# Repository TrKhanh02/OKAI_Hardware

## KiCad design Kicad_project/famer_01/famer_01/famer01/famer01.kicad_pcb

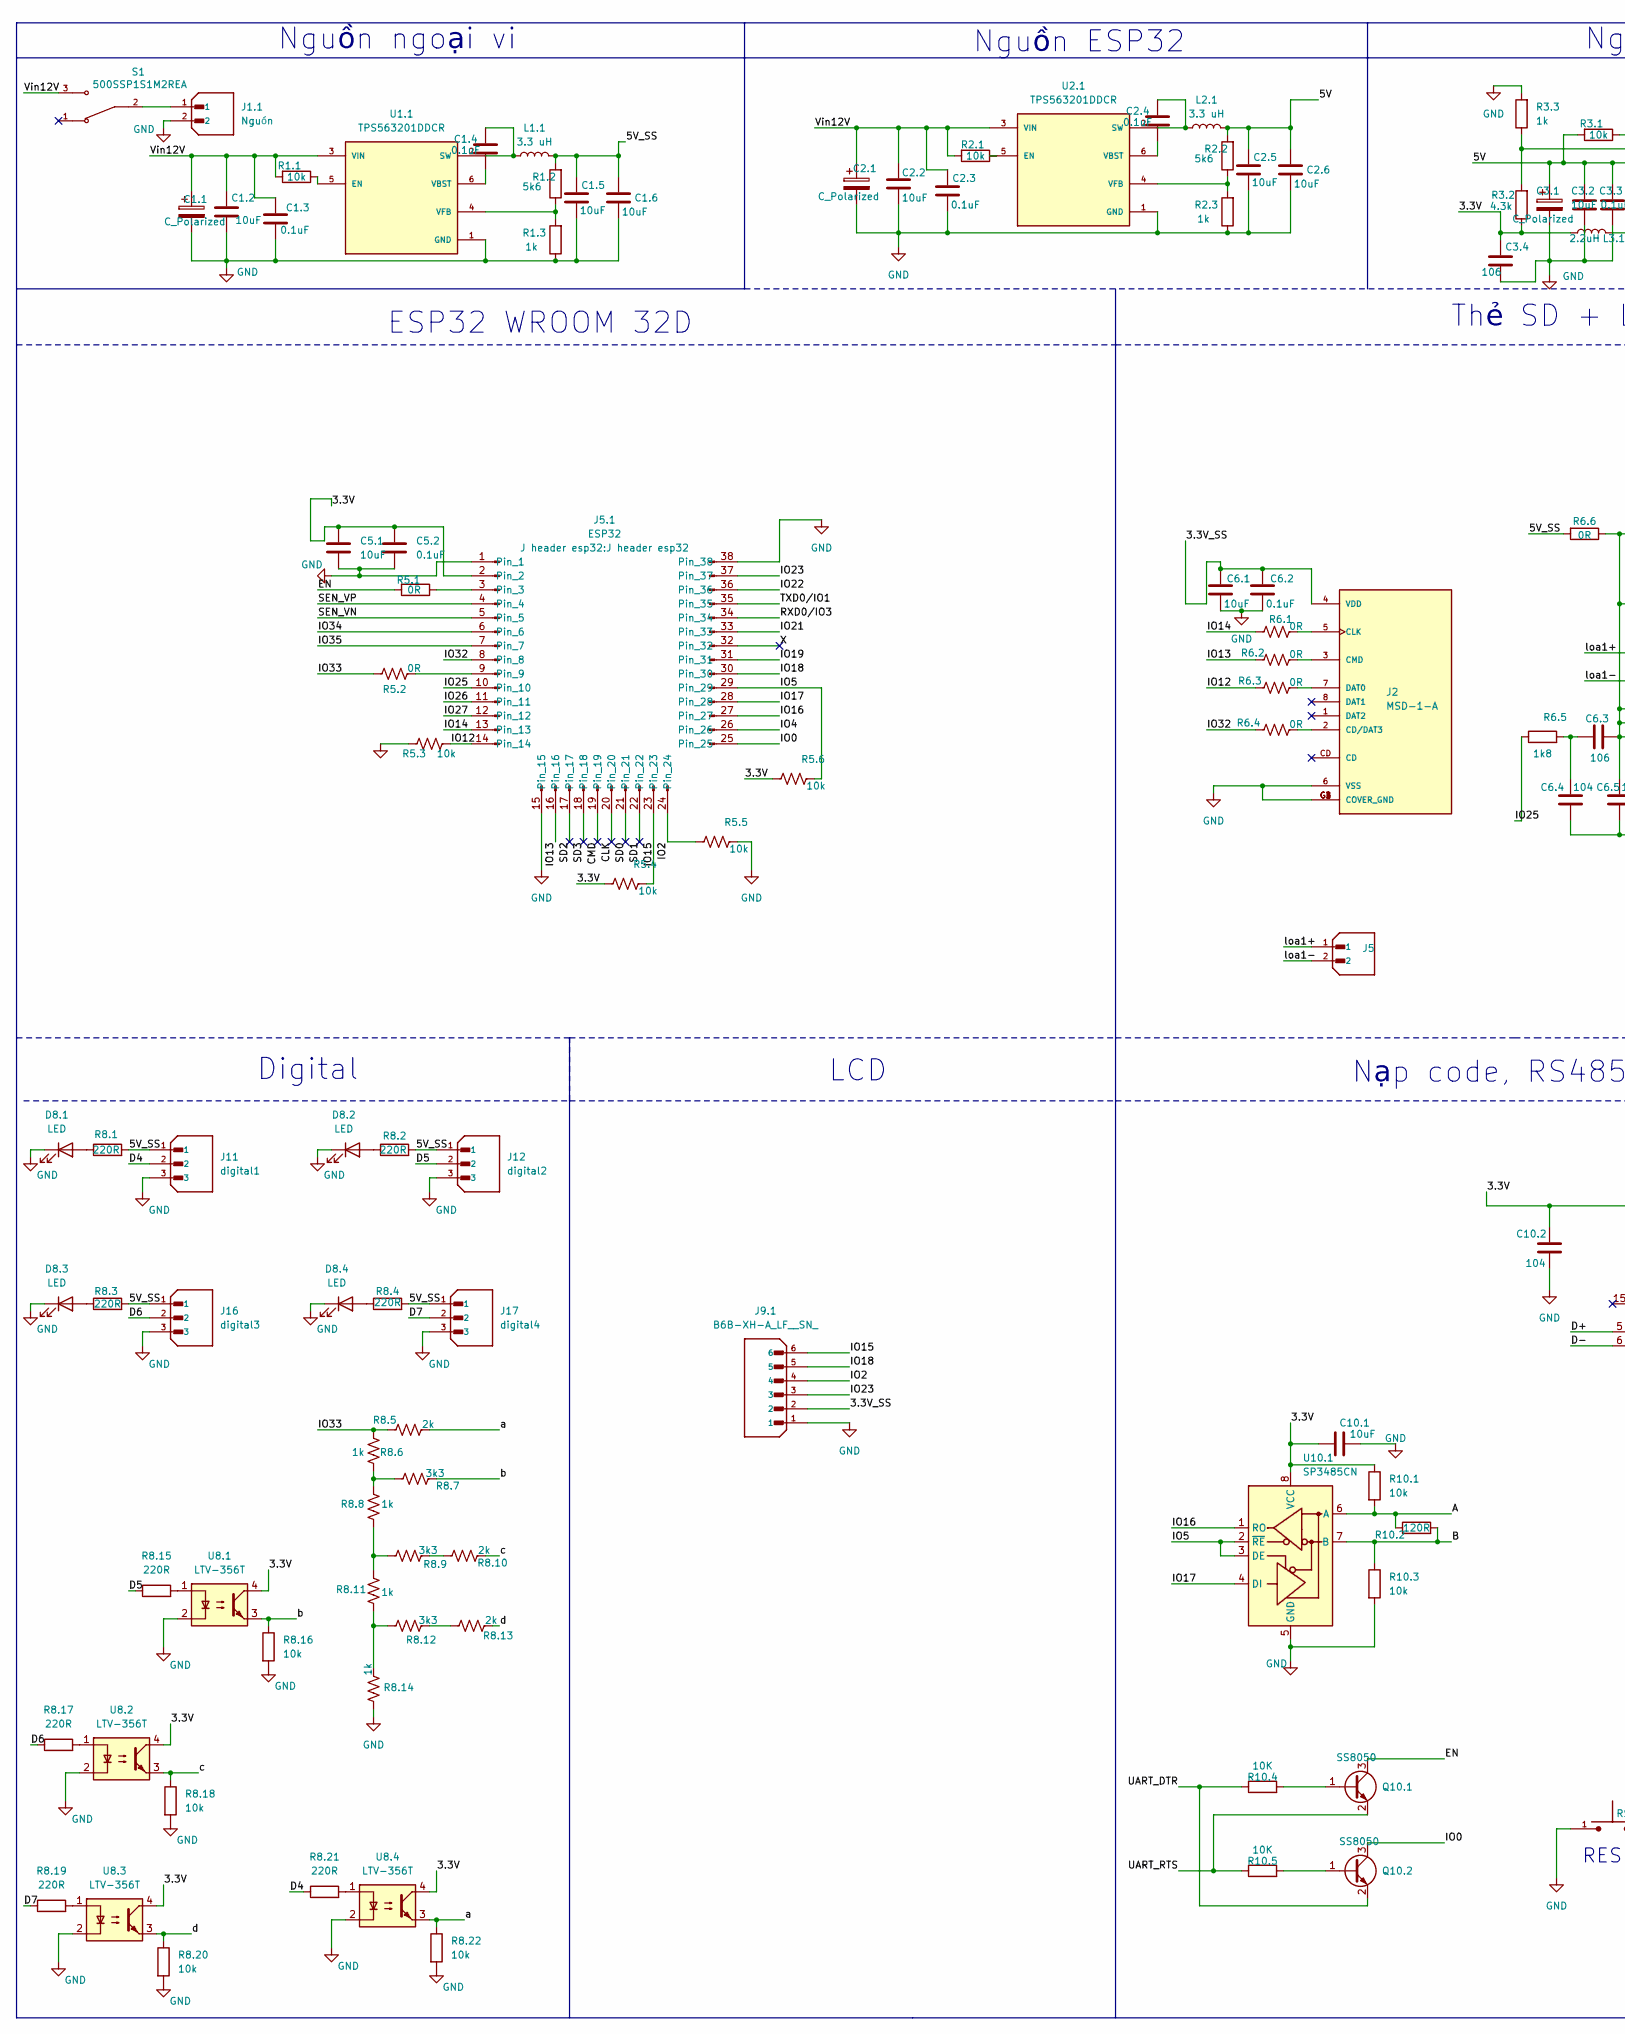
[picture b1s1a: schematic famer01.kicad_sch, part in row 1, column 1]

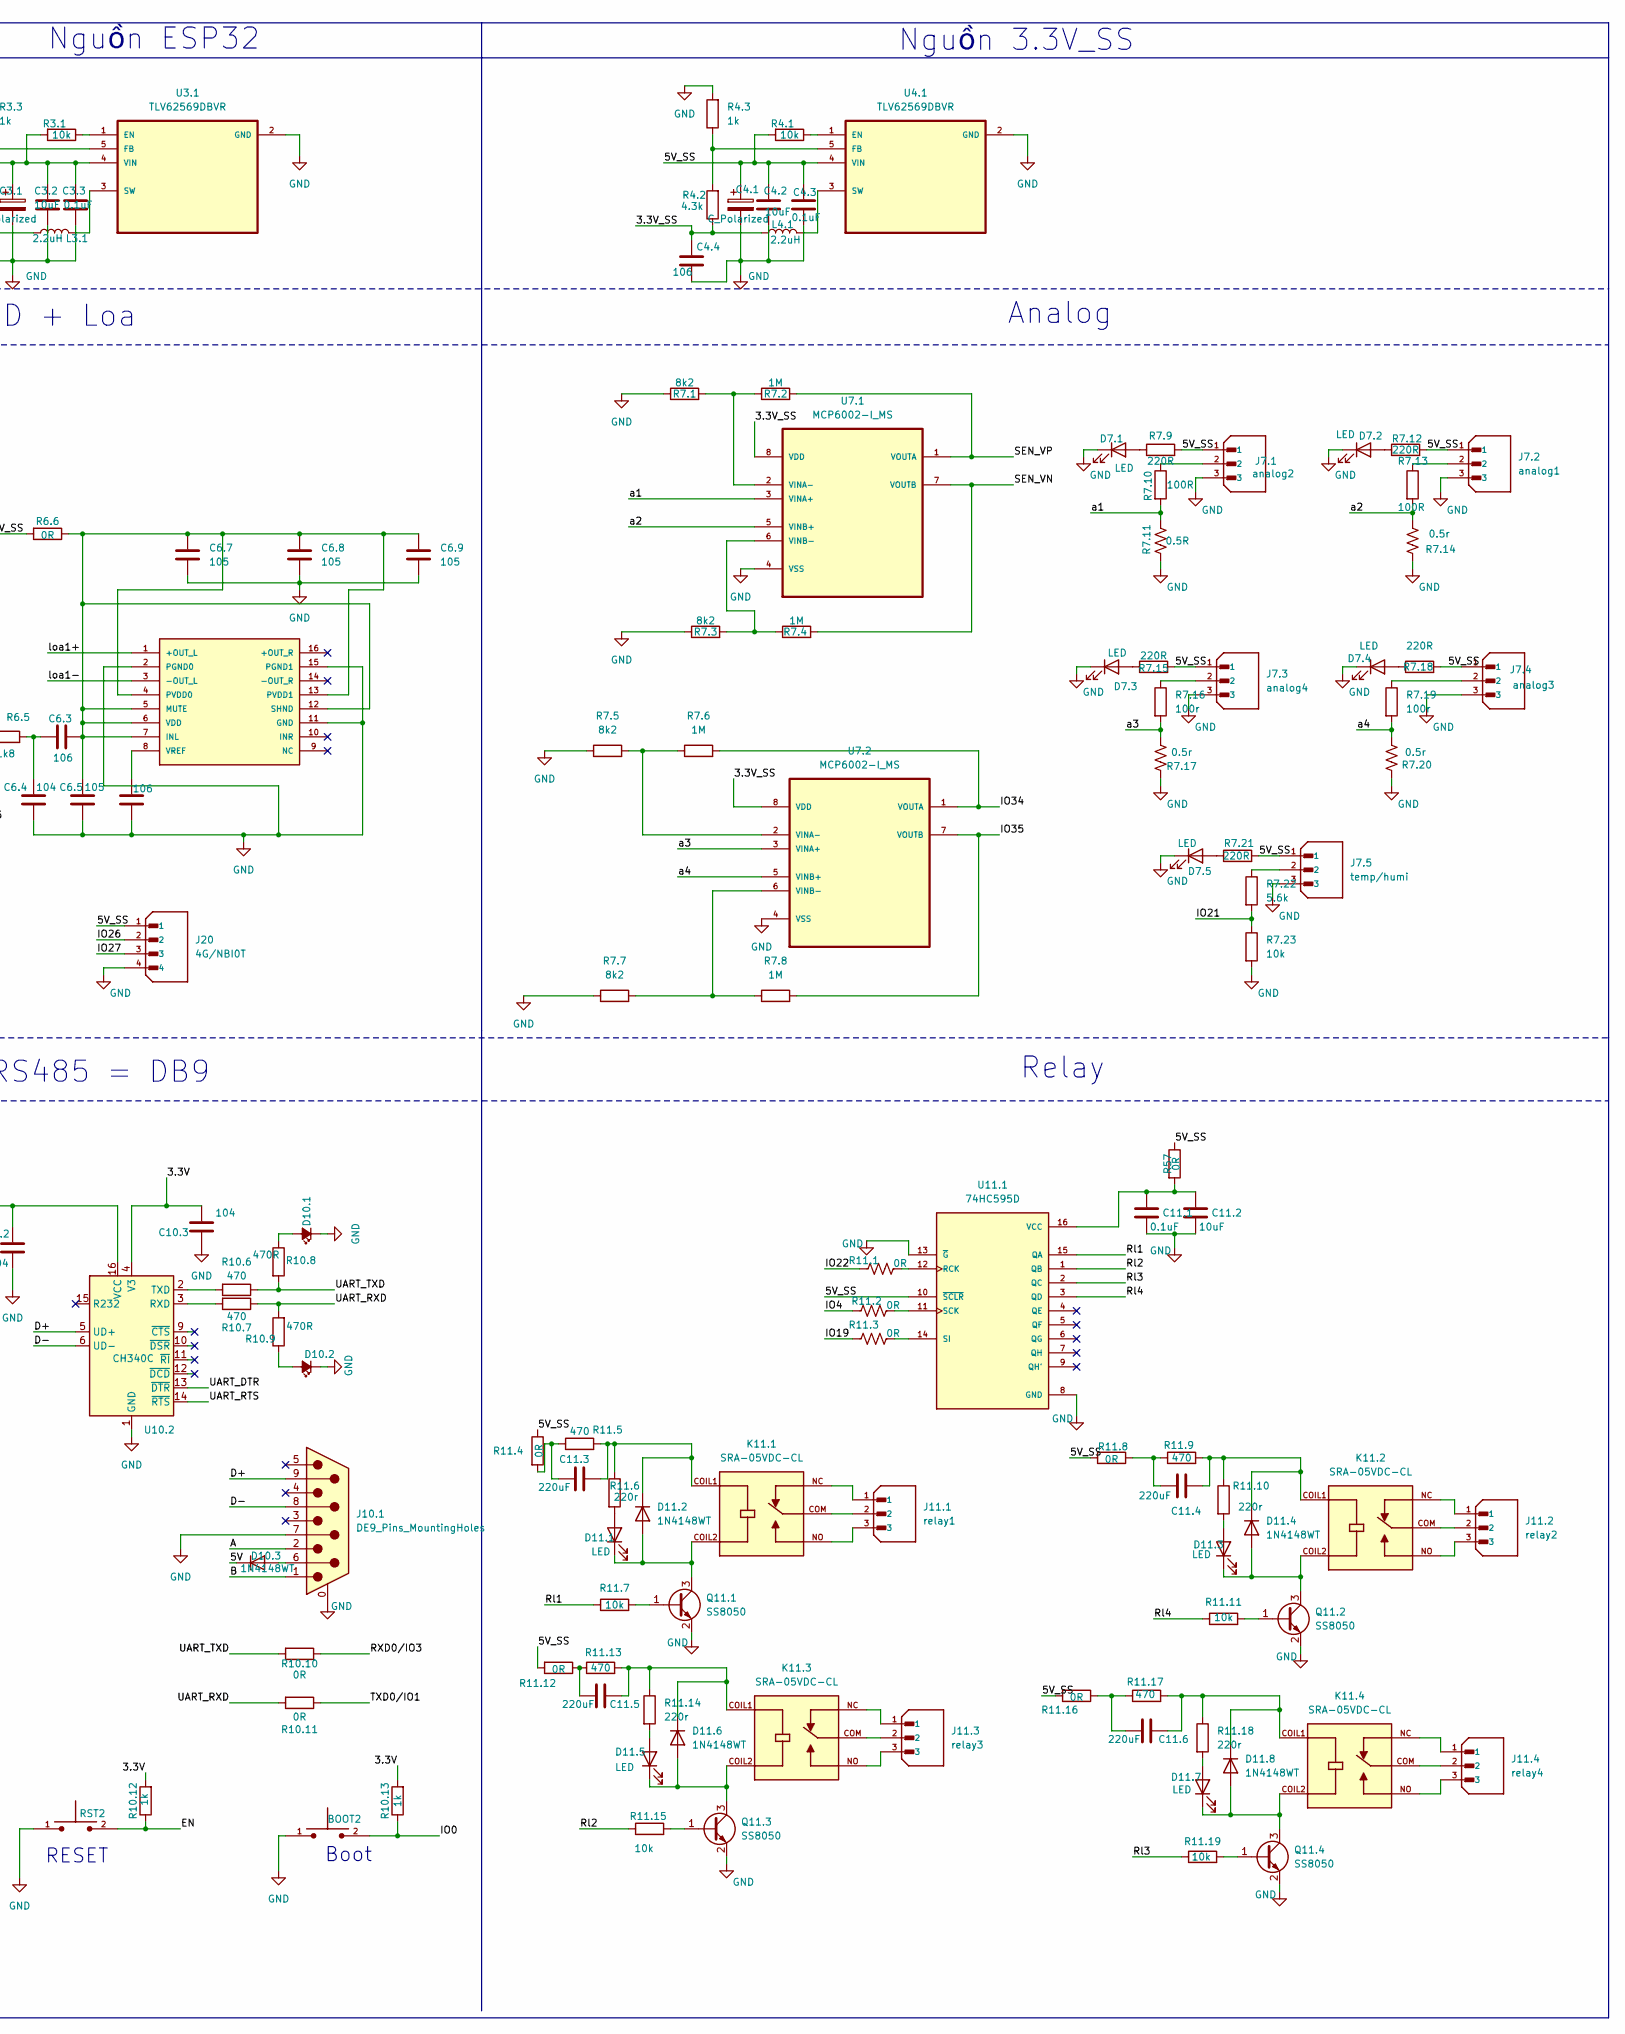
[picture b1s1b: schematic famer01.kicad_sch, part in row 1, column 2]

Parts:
BOOT2: TS10-63-26-BE-250-SMT-TR; SW_TS10-63-26-BE-250-SMT-TR; PARTREV 1.0
C1.1, C2.1, C3.1, C4.1: C_Polarized; CP_Elec_6.3x7.7
C1.2, C1.5, C1.6, C2.2, C2.5, C2.6, C3.2, C4.2, C5.1, C6.1, C10.1, C11.2: 10uF; C_0805_2012Metric_Pad1.18x1.45mm_HandSolder
C1.3, C1.4, C2.3, C2.4, C3.3, C4.3, C5.2, C6.2, C11.1: 0.1uF; C_0805_2012Metric_Pad1.18x1.45mm_HandSolder
C3.4, C4.4, C6.3, C6.6: 106; C_0805_2012Metric_Pad1.18x1.45mm_HandSolder
C6.4, C10.2, C10.3: 104; C_0805_2012Metric_Pad1.18x1.45mm_HandSolder
C6.5, C6.7, C6.8, C6.9: 105; C_0805_2012Metric_Pad1.18x1.45mm_HandSolder
C11.3, C11.4, C11.5, C11.6: 220uF; C_0805_2012Metric_Pad1.18x1.45mm_HandSolder
D7.1, D7.2, D7.3, D7.4, D7.5, D8.1, D8.2, D8.3, D8.4, D11.1, D11.3, D11.5, D11.7: LED; LED_Rectangular_W3.0mm_H2.0mm
D10.1, D10.2: LED_Small_Filled; LED_0805_2012Metric_Pad1.15x1.40mm_HandSolder
D10.3, D11.2, D11.4, D11.6, D11.8: 1N4148WT; D_0805_2012Metric_Pad1.15x1.40mm_HandSolder
J1.1: Nguồn; CUI_TBP04R1-500-02BE; PARTREV N/A
J2: MSD-1-A; CUI_MSD-1-A; PARTREV 1.0
J5: Nguồn; JST_B2B-XH-A; PARTREV N/A
J5.1: ESP32; J header esp32
J7.1: analog2; CUI_TBP04R1-500-03BE; PARTREV 7/4/21
J7.2: analog1; CUI_TBP04R1-500-03BE; PARTREV 7/4/21
J7.3: analog4; CUI_TBP04R1-500-03BE; PARTREV 7/4/21
J7.4: analog3; CUI_TBP04R1-500-03BE; PARTREV 7/4/21
J7.5: temp/humi; CUI_TBP04R1-500-03BE; PARTREV 7/4/21
J9.1: B6B-XH-A_LF__SN_; JST_B6B-XH-A_LF__SN_; PARTREV 7/4/21
J10.1: DE9_Pins_MountingHoles; DSUB-9_Pins_Vertical_P2.77x2.84mm_MountingHoles
J11: digital1; CUI_TBP04R1-500-03BE; PARTREV 7/4/21
J11.1: relay1; CUI_TBP04R1-500-03BE; PARTREV 7/4/21
J11.2: relay2; CUI_TBP04R1-500-03BE; PARTREV 7/4/21
J11.3: relay3; CUI_TBP04R1-500-03BE; PARTREV 7/4/21
J11.4: relay4; CUI_TBP04R1-500-03BE; PARTREV 7/4/21
J12: digital2; CUI_TBP04R1-500-03BE; PARTREV 7/4/21
J16: digital3; CUI_TBP04R1-500-03BE; PARTREV 7/4/21
J17: digital4; CUI_TBP04R1-500-03BE; PARTREV 7/4/21
J20: 4G/NBI0T; JST_B4B-XH-A_LF__SN_; PARTREV 7/4/21
K11.1, K11.2, K11.3, K11.4: SRA-05VDC-CL; RELAY_SRA-05VDC-CL; PARTREV NA
L1.1, L2.1: 3.3 uH; IND_SLF7032T-331MR22-2PF
L3.1, L4.1: 2.2uH; IND_SLF7032T-331MR22-2PF
Q10.1, Q10.2, Q11.1, Q11.2, Q11.3, Q11.4: SS8050; SOT-23
R1.1, R2.1, R3.1, R4.1, R5.3, R5.4, R5.5, R5.6, R7.23, R8.16, R8.18, R8.20, R8.22, R10.1, R10.3, R11.7, R11.11, R11.15, R11.19: 10k; R_0805_2012Metric_Pad1.20x1.40mm_HandSolder
R1.2, R2.2: 5k6; R_0805_2012Metric_Pad1.20x1.40mm_HandSolder
R1.3, R2.3, R3.3, R4.3, R8.6, R8.8, R8.11, R8.14, R10.12, R10.13: 1k; R_0805_2012Metric_Pad1.20x1.40mm_HandSolder
R3.2, R4.2: 4.3k; R_0805_2012Metric_Pad1.20x1.40mm_HandSolder
R5.1, R5.2, R6.1, R6.2, R6.3, R6.4, R6.6, R10.10, R10.11, R11.1, R11.2, R11.3, R11.4, R11.8, R11.12, R11.16, R57: 0R; R_0805_2012Metric_Pad1.20x1.40mm_HandSolder
R6.5: 1k8; R_0805_2012Metric_Pad1.20x1.40mm_HandSolder
R7.1, R7.3, R7.5, R7.7: 8k2; R_0805_2012Metric_Pad1.20x1.40mm_HandSolder
R7.2, R7.4, R7.6, R7.8: 1M; R_0805_2012Metric_Pad1.20x1.40mm_HandSolder
R7.9, R7.12, R7.15, R7.18, R7.21, R8.1, R8.2, R8.3, R8.4, R8.15, R8.17, R8.19, R8.21: 220R; R_0805_2012Metric_Pad1.20x1.40mm_HandSolder
R7.10, R7.13: 100R; R_0805_2012Metric_Pad1.20x1.40mm_HandSolder
R7.11: 0.5R; R_2512_6332Metric_Pad1.40x3.35mm_HandSolder
R7.14, R7.17, R7.20: 0.5r; R_2512_6332Metric_Pad1.40x3.35mm_HandSolder
R7.16, R7.19: 100r; R_0805_2012Metric_Pad1.20x1.40mm_HandSolder
R7.22: 5.6k; R_0805_2012Metric_Pad1.20x1.40mm_HandSolder
R8.5, R8.10, R8.13: 2k; R_0805_2012Metric_Pad1.20x1.40mm_HandSolder
R8.7, R8.9, R8.12: 3k3; R_0805_2012Metric_Pad1.20x1.40mm_HandSolder
R10.2: 120R; R_0805_2012Metric_Pad1.20x1.40mm_HandSolder
R10.4, R10.5: 10K; R_0805_2012Metric_Pad1.20x1.40mm_HandSolder
R10.6, R10.7, R11.5, R11.9, R11.13, R11.17: 470; R_0805_2012Metric_Pad1.20x1.40mm_HandSolder
R10.8, R10.9: 470R; R_0805_2012Metric_Pad1.20x1.40mm_HandSolder
R11.6, R11.10, R11.14, R11.18: 220r; R_0805_2012Metric_Pad1.20x1.40mm_HandSolder
RST2: TS10-63-26-BE-250-SMT-TR; SW_TS10-63-26-BE-250-SMT-TR; PARTREV 1.0
S1: 500SSP1S1M2REA; PinHeader_1x03_P2.54mm_Vertical
U1: PAM8403; SOP-16
U1.1, U2.1: TPS563201DDCR; SOT95P280X110-6N; PARTREV December 2015
U3.1, U4.1: TLV62569DBVR; SOT95P280X145-5N
U7.1, U7.2: MCP6002-I_MS; SOP65P490X110-8N; MPN MCP6002-I/MS
U8.1, U8.2, U8.3, U8.4: LTV-356T; SO-4_4.4x3.6mm_P2.54mm
U10.1: SP3485CN; SOIC-8_3.9x4.9mm_P1.27mm
U10.2: CH340C; SOIC-16_3.9x9.9mm_P1.27mm
U11.1: 74HC595D; SOP127P600X175-16N; PARTREV 4.0

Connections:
/3.3V: C3.4.1, C5.1.1, C5.2.1, C10.1.1, C10.2.2, C10.3.2, J5.1.2, L3.1.1, R3.2.1, R5.4.1, R5.6.1, R10.1.1, R10.12.2, R10.13.2, U8.1.4, U8.2.4, U8.3.4, U8.4.4, U10.1.8 (VCC), U10.2.4 (V3), U10.2.16 (VCC)
/3.3V_SS: C4.4.1, C6.1.1, C6.2.1, J2.4 (VDD), J9.1.2, L4.1.1, R4.2.1, U7.1.8 (VDD), U7.2.8 (VDD)
/5V: C2.5.1, C2.6.1, C3.1.1, C3.2.1, C3.3.1, D10.3.1 (K), L2.1.2, R2.2.2, R3.1.2, U3.1.4 (VIN)
/5V_SS: C1.5.1, C1.6.1, C4.1.1, C4.2.1, C4.3.1, J7.1.1, J7.2.1, J7.3.1, J7.4.1, J7.5.1, J11.1, J12.1, J16.1, J17.1, J20.1, L1.1.2, R1.2.2, R4.1.2, R6.6.2, R7.9.2, R7.12.2, R7.15.2, R7.18.2, R7.21.2, R8.1.2, R8.2.2, R8.3.2, R8.4.2, R11.4.1, R11.8.2, R11.12.2, R11.16.2, R57.1, U4.1.4 (VIN), U11.1.10 (~SCLR)
/ A: J10.1.2, R10.1.2, R10.2.1, U10.1.6 (A)
/ B: J10.1.1, R10.2.2, R10.3.1, U10.1.7 (B)
/D4: J11.2, R8.21.1
/D5: J12.2, R8.15.1
/D6: J16.2, R8.17.1
/D7: J17.2, R8.19.1
/D+: J10.1.9, U10.2.5 (UD+)
/D-: J10.1.8, U10.2.6 (UD-)
/EN: Q10.1.3 (C), R5.1.2, R10.12.1, RST2.2
/IO0: BOOT2.2, J5.1.25, Q10.2.3 (C), R10.13.1
/IO2: J5.1.24, J9.1.4, R5.5.1
/IO4: J5.1.26, R11.2.1
/IO5: J5.1.29, R5.6.2, U10.1.2 (~RE), U10.1.3 (DE)
/IO12: J5.1.14, R5.3.2, R6.3.1
/IO13: J5.1.16, R6.2.1
/IO14: J5.1.13, R6.1.1
/IO15: J5.1.23, J9.1.6, R5.4.2
/IO16: J5.1.27, U10.1.1 (RO)
/IO17: J5.1.28, U10.1.4 (DI)
/IO18: J5.1.30, J9.1.5
/IO19: J5.1.31, R11.3.1
/IO21: J5.1.33, R7.22.2, R7.23.1
/IO22: J5.1.36, R11.1.1
/IO23: J5.1.37, J9.1.3
/IO25: J5.1.10, R6.5.1
/IO26: J5.1.11, J20.2
/IO27: J5.1.12, J20.3
/IO32: J5.1.8, R6.4.1
/IO33: R5.2.1, R8.5.1, R8.6.2
/IO34: J5.1.6, R7.6.2, U7.2.1 (VOUTA)
/IO35: J5.1.7, R7.8.2, U7.2.7 (VOUTB)
/RXD0/IO3: J5.1.34, R10.10.1
/Rl1: R11.7.1, U11.1.15 (QA)
/Rl2: R11.15.1, U11.1.1 (QB)
/Rl3: R11.19.1, U11.1.2 (QC)
/Rl4: R11.11.1, U11.1.3 (QD)
/SEN_VN: J5.1.5, R7.4.2, U7.1.7 (VOUTB)
/SEN_VP: J5.1.4, R7.2.2, U7.1.1 (VOUTA)
/TXD0/IO1: J5.1.35, R10.11.1
/UART_DTR: Q10.2.2 (E), R10.4.1, U10.2.13 (~DTR)
/UART_RTS: Q10.1.2 (E), R10.5.1, U10.2.14 (~RTS)
/UART_RXD: R10.7.1, R10.9.2, R10.11.2
/UART_TXD: R10.6.1, R10.8.2, R10.10.2
/Vin12V: C1.1.1, C1.2.1, C1.3.1, C2.1.1, C2.2.1, C2.3.1, R1.1.2, R2.1.2, S1.3, U1.1.3 (VIN), U2.1.3 (VIN)
/a: R8.5.2, R8.22.1, U8.4.3
/a1: R7.10.2, R7.11.2, U7.1.3 (VINA+)
/a2: R7.13.2, R7.14.1, U7.1.5 (VINB+)
/a3: R7.16.2, R7.17.1, U7.2.3 (VINA+)
/a4: R7.19.2, R7.20.1, U7.2.5 (VINB+)
/b: R8.7.2, R8.16.1, U8.1.3
/c: R8.10.2, R8.18.1, U8.2.3
/d: R8.13.2, R8.20.1, U8.3.3
/loa1+: J5.1, U1.1 (+OUT_L)
/loa1-: J5.2, U1.3 (-OUT_L)
GND: BOOT2.1, C1.1.2, C1.2.2, C1.3.2, C1.5.2, C1.6.2, C2.1.2, C2.2.2, C2.3.2, C2.5.2, C2.6.2, C3.1.2, C3.2.2, C3.3.2, C3.4.2, C4.1.2, C4.2.2, C4.3.2, C4.4.2, C5.1.2, C5.2.2, C6.1.2, C6.2.2, C6.4.2, C6.5.1, C6.6.1, C6.7.1, C6.8.1, C6.9.1, C10.1.2, C10.2.1, C10.3.1, C11.1.2, C11.2.2, D7.1.1 (K), D7.2.1 (K), D7.3.1 (K), D7.4.1 (K), D7.5.1 (K), D8.1.1 (K), D8.2.1 (K), D8.3.1 (K), D8.4.1 (K), D10.1.1 (K), D10.2.1 (K), J1.1.2, J2.6 (VSS), J2.G1 (COVER_GND), J2.G2 (COVER_GND), J2.G3 (COVER_GND), J2.G4 (COVER_GND), J5.1.1, J5.1.15, J5.1.38, J7.1.3, J7.2.3, J7.3.3, J7.4.3, J7.5.3, J9.1.1, J10.1.0 (PAD), J10.1.7, J11.3, J12.3, J16.3, J17.3, J20.4, Q11.1.2 (E), Q11.2.2 (E), Q11.3.2 (E), Q11.4.2 (E), R1.3.1, R2.3.1, R3.3.2, R4.3.2, R5.3.1, R5.5.2, R7.1.1, R7.3.1, R7.5.1, R7.7.1, R7.11.1, R7.14.2, R7.17.2, R7.20.2, R7.23.2, R8.14.1, R8.16.2, R8.18.2, R8.20.2, R8.22.2, R10.3.2, RST2.1, U1.2 (PGND0), U1.11 (GND), U1.15 (PGND1), U1.1.1 (GND), U2.1.1 (GND), U3.1.2 (GND), U4.1.2 (GND), U7.1.4 (VSS), U7.2.4 (VSS), U8.1.2, U8.2.2, U8.3.2, U8.4.2, U10.1.5 (GND), U10.2.1 (GND), U11.1.8 (GND), U11.1.13 (~G)
unnamed: C6.3.2, C6.4.1, R6.5.2
unnamed: C11.3.2, R11.4.2, R11.5.1
unnamed: C11.4.2, R11.8.1, R11.9.1
unnamed: C11.5.2, R11.12.1, R11.13.1
unnamed: C11.6.2, R11.16.1, R11.17.1
unnamed: D7.1.2 (A), R7.9.1
unnamed: D7.2.2 (A), R7.12.1
unnamed: D7.3.2 (A), R7.15.1
unnamed: D7.4.2 (A), R7.18.1
unnamed: D7.5.2 (A), R7.21.1
unnamed: D8.1.2 (A), R8.1.1
unnamed: D8.2.2 (A), R8.2.1
unnamed: D8.3.2 (A), R8.3.1
unnamed: D8.4.2 (A), R8.4.1
unnamed: D10.1.2 (A), R10.8.1
unnamed: D10.2.2 (A), R10.9.1
unnamed: D10.3.2 (A), J10.1.6
unnamed: D11.1.2 (A), R11.6.2
unnamed: D11.1.1 (K), D11.2.2 (A), K11.1.COIL2, Q11.1.3 (C)
unnamed: C11.3.1, D11.2.1 (K), K11.1.COIL1, R11.5.2, R11.6.1
unnamed: D11.3.2 (A), R11.10.2
unnamed: D11.3.1 (K), D11.4.2 (A), K11.2.COIL2, Q11.2.3 (C)
unnamed: C11.4.1, D11.4.1 (K), K11.2.COIL1, R11.9.2, R11.10.1
unnamed: D11.5.2 (A), R11.14.2
unnamed: D11.5.1 (K), D11.6.2 (A), K11.3.COIL2, Q11.3.3 (C)
unnamed: C11.5.1, D11.6.1 (K), K11.3.COIL1, R11.13.2, R11.14.1
unnamed: D11.7.2 (A), R11.18.2
unnamed: D11.7.1 (K), D11.8.2 (A), K11.4.COIL2, Q11.4.3 (C)
unnamed: C11.6.1, D11.8.1 (K), K11.4.COIL1, R11.17.2, R11.18.1
unnamed: J1.1.1, S1.2
unnamed: J2.2 (CD/DAT3), R6.4.2
unnamed: J2.5 (CLK), R6.1.2
unnamed: J2.3 (CMD), R6.2.2
unnamed: J2.7 (DAT0), R6.3.2
unnamed: J5.1.3, R5.1.1
unnamed: J5.1.9, R5.2.2
unnamed: J7.1.2, R7.10.1
unnamed: J7.2.2, R7.13.1
unnamed: J7.3.2, R7.16.1
unnamed: J7.4.2, R7.19.1
unnamed: J7.5.2, R7.22.1
unnamed: J11.1.1, K11.1.NC
unnamed: J11.1.2, K11.1.COM
unnamed: J11.1.3, K11.1.NO
unnamed: J11.2.1, K11.2.NC
unnamed: J11.2.2, K11.2.COM
unnamed: J11.2.3, K11.2.NO
unnamed: J11.3.1, K11.3.NC
unnamed: J11.3.2, K11.3.COM
unnamed: J11.3.3, K11.3.NO
unnamed: J11.4.1, K11.4.NC
unnamed: J11.4.2, K11.4.COM
unnamed: J11.4.3, K11.4.NO
unnamed: Q10.1.1 (B), R10.4.2
unnamed: Q10.2.1 (B), R10.5.2
unnamed: Q11.1.1 (B), R11.7.2
unnamed: Q11.2.1 (B), R11.11.2
unnamed: Q11.3.1 (B), R11.15.2
unnamed: Q11.4.1 (B), R11.19.2
unnamed: R8.6.1, R8.7.1, R8.8.2
unnamed: R8.9.2, R8.10.1
unnamed: R8.11.1, R8.12.1, R8.14.2
unnamed: R8.8.1, R8.9.1, R8.11.2
unnamed: R8.12.2, R8.13.1
unnamed: R8.15.2, U8.1.1
unnamed: R8.17.2, U8.2.1
unnamed: R8.19.2, U8.3.1
unnamed: R8.21.2, U8.4.1
unnamed: C6.3.1, C6.5.2, C6.7.2, C6.8.2, C6.9.2, R6.6.1, U1.4 (PVDD0), U1.5 (MUTE), U1.6 (VDD), U1.7 (INL), U1.12 (SHND), U1.13 (PVDD1)
unnamed: C6.6.2, U1.8 (VREF)
unnamed: R1.1.1, U1.1.5 (EN)
unnamed: C1.4.1, L1.1.1, U1.1.2 (SW)
unnamed: C1.4.2, U1.1.6 (VBST)
unnamed: R1.2.1, R1.3.2, U1.1.4 (VFB)
unnamed: R2.1.1, U2.1.5 (EN)
unnamed: C2.4.1, L2.1.1, U2.1.2 (SW)
unnamed: C2.4.2, U2.1.6 (VBST)
unnamed: R2.2.1, R2.3.2, U2.1.4 (VFB)
unnamed: R3.1.1, U3.1.1 (EN)
unnamed: R3.2.2, R3.3.1, U3.1.5 (FB)
unnamed: L3.1.2, U3.1.3 (SW)
unnamed: R4.1.1, U4.1.1 (EN)
unnamed: R4.2.2, R4.3.1, U4.1.5 (FB)
unnamed: L4.1.2, U4.1.3 (SW)
unnamed: R7.1.2, R7.2.1, U7.1.2 (VINA-)
unnamed: R7.3.2, R7.4.1, U7.1.6 (VINB-)
unnamed: R7.5.2, R7.6.1, U7.2.2 (VINA-)
unnamed: R7.7.2, R7.8.1, U7.2.6 (VINB-)
unnamed: R10.7.2, U10.2.3 (RXD)
unnamed: R10.6.2, U10.2.2 (TXD)
unnamed: R11.1.2, U11.1.12 (RCK)
unnamed: R11.2.2, U11.1.11 (SCK)
unnamed: R11.3.2, U11.1.14 (SI)
unnamed: C11.1.1, C11.2.1, R57.2, U11.1.16 (VCC)

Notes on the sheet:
Relay
Analog
Nạp code, RS485 = DB9
Nguồn ngoại vi
LCD
Nguồn ESP32
Boot
RESET
Thẻ SD + Loa
ESP32 WROOM 32D
Digital
Nguồn 3.3V_SS

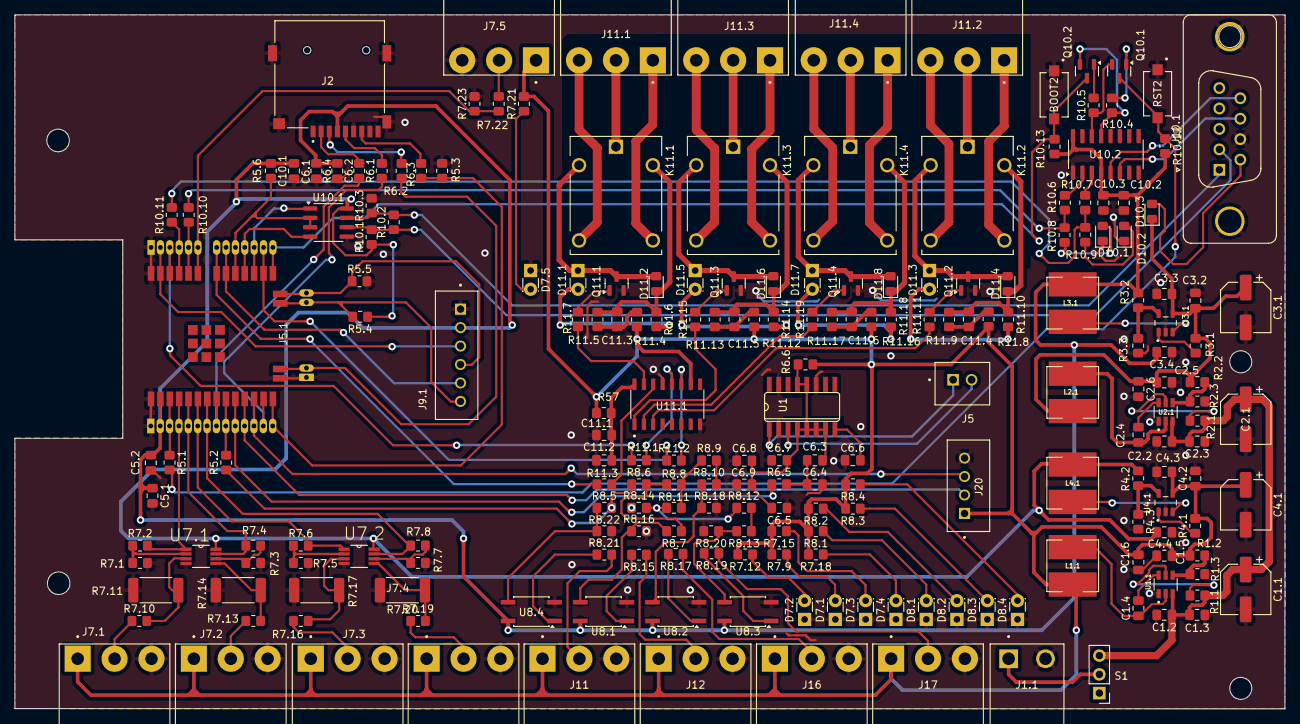
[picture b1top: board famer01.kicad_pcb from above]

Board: 2 copper layers, 172.1 x 94.0 mm, 213 parts (0 on the bottom side), 153 nets.

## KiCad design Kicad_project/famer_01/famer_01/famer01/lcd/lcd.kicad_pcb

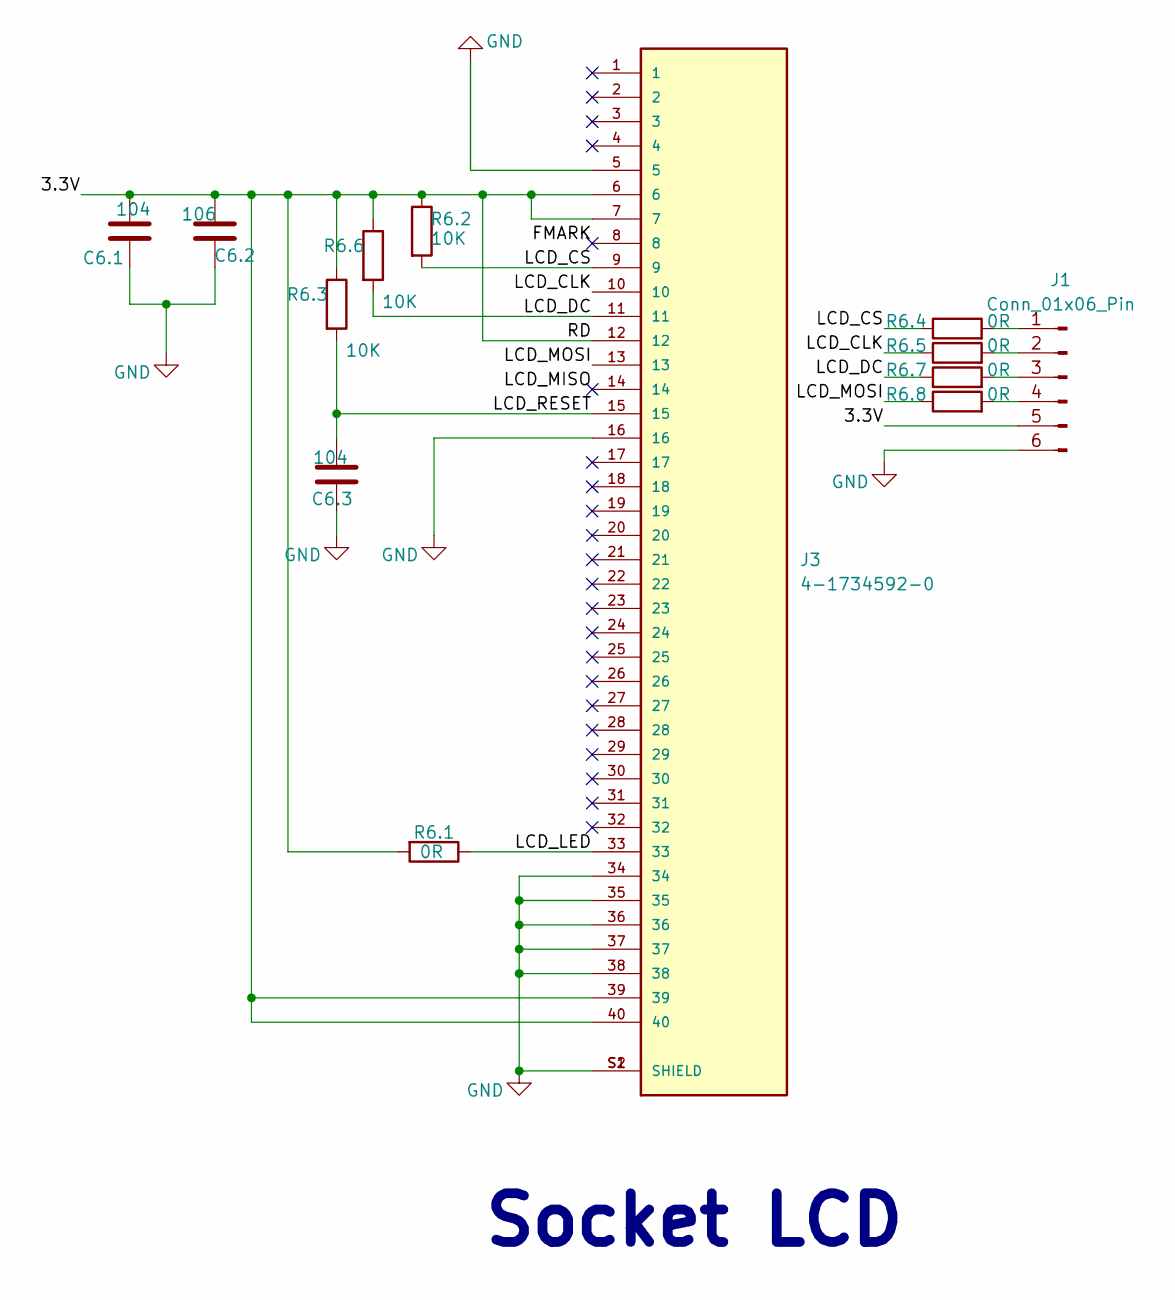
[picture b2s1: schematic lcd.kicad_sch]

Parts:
C6.1, C6.3: 104; C_0805_2012Metric_Pad1.18x1.45mm_HandSolder
C6.2: 106; C_0805_2012Metric_Pad1.18x1.45mm_HandSolder
J1: Conn_01x06_Pin; PinSocket_1x06_P2.54mm_Vertical
J3: 4-1734592-0; TE_4-1734592-0; PARTREV C
R6.1, R6.4, R6.5, R6.7, R6.8: 0R; R_0805_2012Metric_Pad1.20x1.40mm_HandSolder
R6.2, R6.3, R6.6: 10K; R_0805_2012Metric_Pad1.20x1.40mm_HandSolder

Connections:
/3.3V: C6.1.2, C6.2.2, J1.5, J3.6, J3.7, J3.12, J3.39, J3.40, R6.1.2, R6.2.1, R6.3.1, R6.6.1
/FMARK: J3.8
/LCD_CLK: J3.10, R6.5.1
/LCD_CS: J3.9, R6.2.2, R6.4.1
/LCD_DC: J3.11, R6.6.2, R6.7.1
/LCD_LED: J3.33, R6.1.1
/LCD_MISO: J3.14
/LCD_MOSI: J3.13, R6.8.1
/LCD_RESET: C6.3.2, J3.15, R6.3.2
GND: C6.1.1, C6.2.1, C6.3.1, J1.6, J3.5, J3.16, J3.34, J3.35, J3.36, J3.37, J3.38, J3.S1 (SHIELD), J3.S2 (SHIELD)
unnamed: J1.1, R6.4.2
unnamed: J1.2, R6.5.2
unnamed: J1.3, R6.7.2
unnamed: J1.4, R6.8.2

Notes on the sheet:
Socket LCD

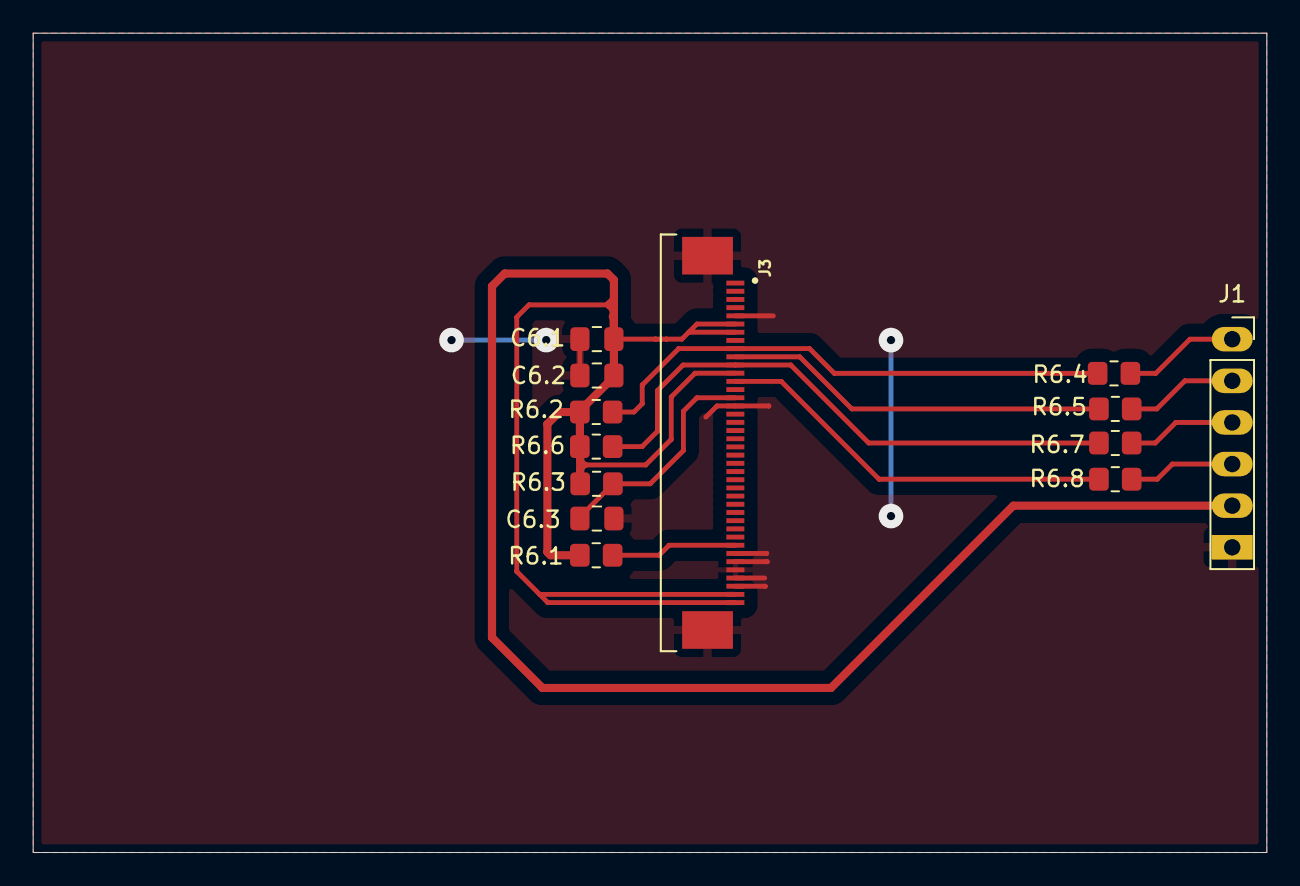
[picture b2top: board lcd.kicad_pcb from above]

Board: 2 copper layers, 75.3 x 50.0 mm, 13 parts (0 on the bottom side), 12 nets.

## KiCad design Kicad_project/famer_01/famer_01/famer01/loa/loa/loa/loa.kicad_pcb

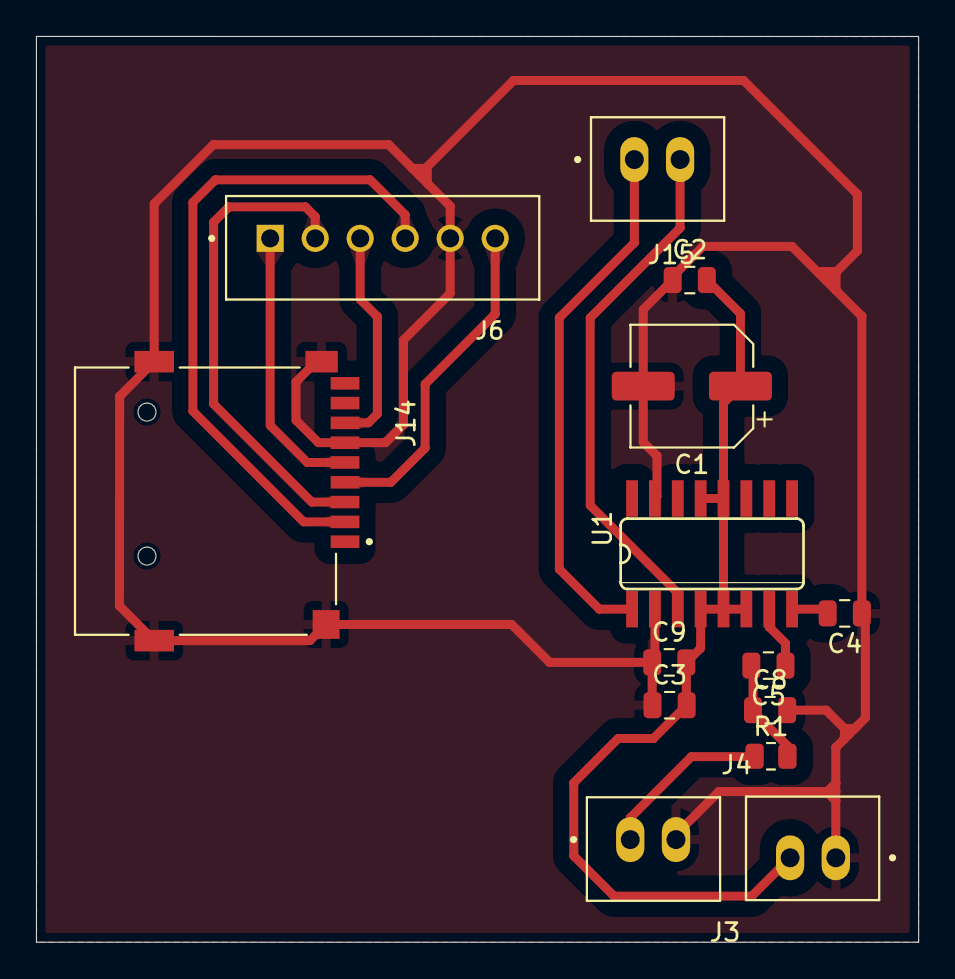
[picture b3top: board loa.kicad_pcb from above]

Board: 2 copper layers, 49.0 x 50.3 mm, 14 parts (0 on the bottom side), 13 nets.

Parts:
C1: 470uf/10V; CP_Elec_6.3x7.7
C2, C3, C9: 105; C_0805_2012Metric
C4, C8: 106; C_0805_2012Metric
C5: 104; C_0805_2012Metric
J3, J4: Conn_01x02_Pin; JST_B2B-XH-A_2.54
J6: B6B-XH-A_LF__SN_; JST_B6B-XH-A_LF__SN_
J14: MSD-1-A; CUI_MSD-1-A
J15: loa; JST_B2B-XH-A_2.54
R1: 1k8; R_0805_2012Metric
U1: PAM8403; SOP-16

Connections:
/3.3v: J6.6, J14.4 (VDD)
/5v: C1.1, C2.2, C3.2, C9.2, J4.2, U1.4 (PVDD0), U1.5 (MUTE), U1.6 (VDD), U1.12 (SHND), U1.13 (PVDD1)
/io18: J6.1, J14.5 (CLK)
/io19: J6.3, J14.7 (DAT0)
/io22: J6.4, J14.2 (CD/DAT3)
/io23: J6.2, J14.3 (CMD)
/loa1+: J15.1, U1.1 (+OUT_L)
/loa1-: J15.2, U1.3 (-OUT_L)
GND: C1.2, C2.1, C3.1, C4.1, C8.2, C9.1, J3.2, J4.1, J6.5, J14.6 (VSS), J14.G1 (COVER_GND), J14.G2 (COVER_GND), J14.G3 (COVER_GND), J14.G4 (COVER_GND), U1.2 (PGND0), U1.15 (PGND1)
unnamed: C5.2, C8.1, R1.2
unnamed: J3.1, R1.1
unnamed: C5.1, U1.7 (INL)
unnamed: C4.2, U1.8 (VREF)

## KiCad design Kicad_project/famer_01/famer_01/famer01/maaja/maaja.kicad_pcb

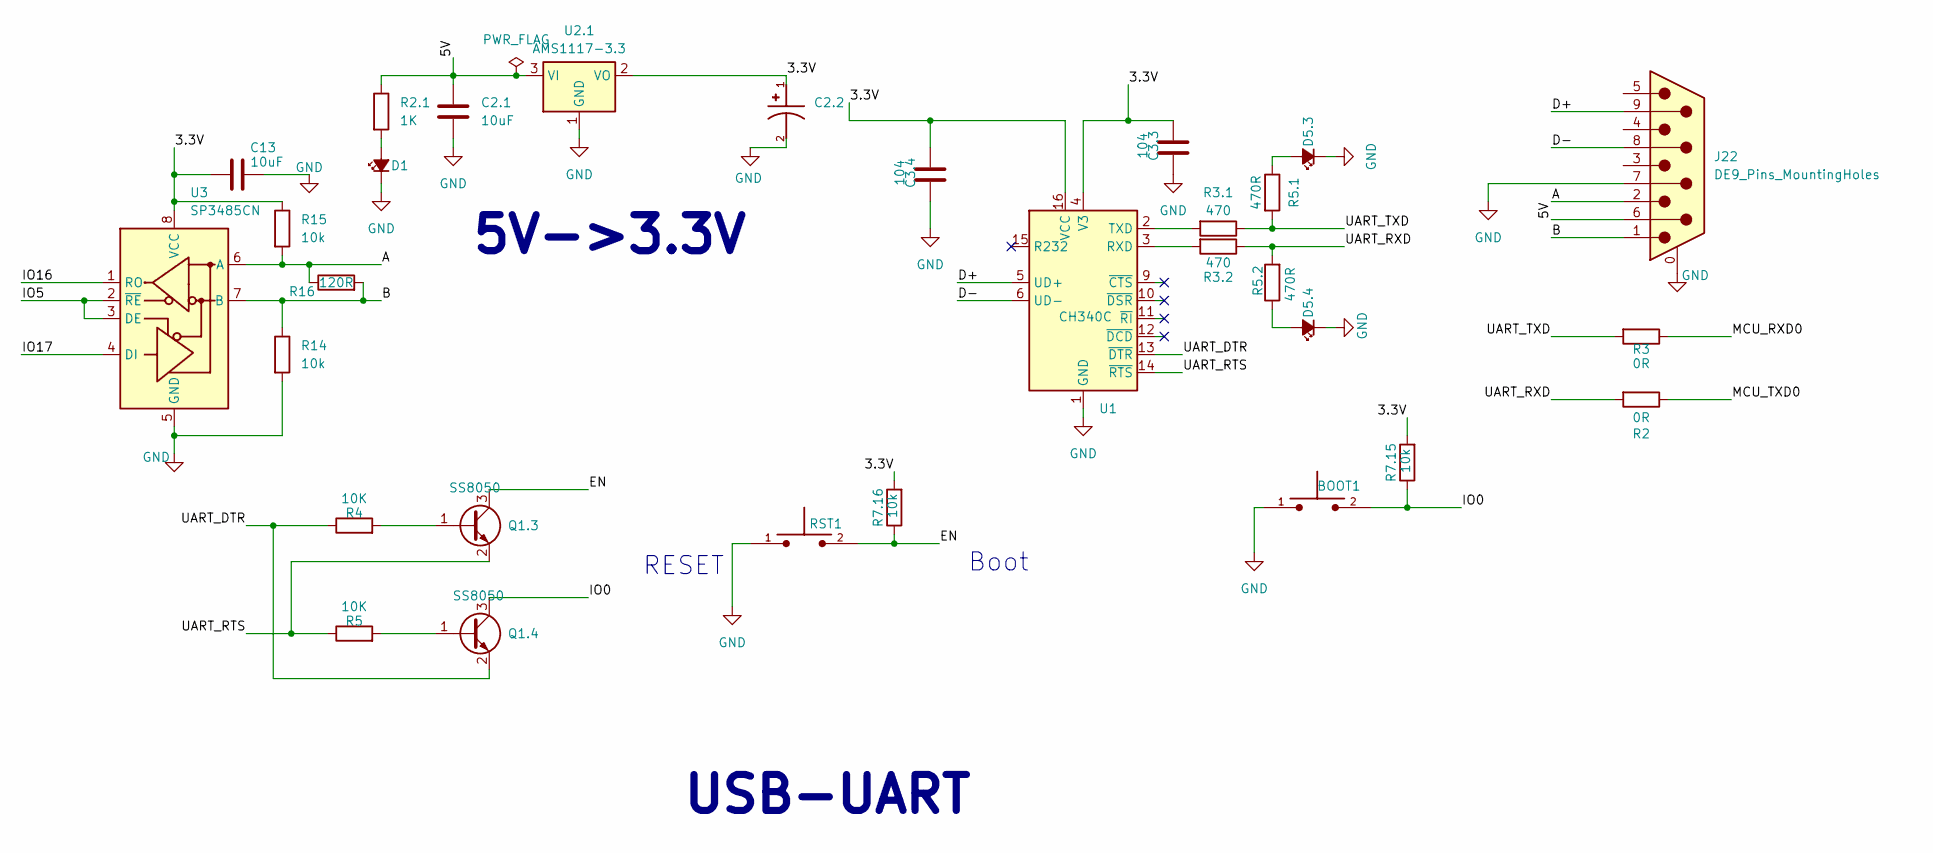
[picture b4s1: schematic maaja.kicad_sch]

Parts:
BOOT1: TS10-63-26-BE-250-SMT-TR; SW_TS10-63-26-BE-250-SMT-TR; PARTREV 1.0
C2.1, C13: 10uF; C_0805_2012Metric_Pad1.18x1.45mm_HandSolder
C2.2: 22uF; CP_EIA-3216-18_Kemet-A_HandSolder; PARTREV 031320
C3.3, C3.4: 104; C_0805_2012Metric_Pad1.18x1.45mm_HandSolder
D1, D5.3, D5.4: LED_Small_Filled; LED_0805_2012Metric_Pad1.15x1.40mm_HandSolder
J22: DE9_Pins_MountingHoles; DSUB-9_Pins_Vertical_P2.77x2.84mm_MountingHoles
Q1.3, Q1.4: SS8050; SOT-23
R2, R3: 0R; R_0805_2012Metric_Pad1.20x1.40mm_HandSolder
R2.1: 1K; R_0805_2012Metric_Pad1.20x1.40mm_HandSolder
R3.1, R3.2: 470; R_0805_2012Metric_Pad1.20x1.40mm_HandSolder
R4, R5: 10K; R_0805_2012Metric_Pad1.20x1.40mm_HandSolder
R5.1, R5.2: 470R; R_0805_2012Metric_Pad1.20x1.40mm_HandSolder
R7.15, R7.16, R14, R15: 10k; R_0805_2012Metric_Pad1.20x1.40mm_HandSolder
R16: 120R; R_0805_2012Metric_Pad1.20x1.40mm_HandSolder
RST1: TS10-63-26-BE-250-SMT-TR; SW_TS10-63-26-BE-250-SMT-TR; PARTREV 1.0
U1: CH340C; SOIC-16_3.9x9.9mm_P1.27mm
U2.1: AMS1117-3.3; SOT-223-3_TabPin2
U3: SP3485CN; SOIC-8_3.9x4.9mm_P1.27mm

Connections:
/3.3V: C2.2.1, C3.3.2, C3.4.2, C13.1, R7.15.2, R7.16.2, R15.1, U1.4 (V3), U1.16 (VCC), U2.1.2 (VO), U3.8 (VCC); also elsewhere on the board
/5V: C2.1.1, J22.6, R2.1.1, U2.1.3 (VI)
/ A: J22.2, R15.2, R16.1, U3.6 (A)
/ B: J22.1, R14.1, R16.2, U3.7 (B)
/D+: J22.9, U1.5 (UD+)
/D-: J22.8, U1.6 (UD-)
/EN: Q1.3.3 (C), R7.16.1, RST1.2; also elsewhere on the board
/IO0: BOOT1.2, Q1.4.3 (C), R7.15.1; also elsewhere on the board
/IO5: U3.2 (~RE), U3.3 (DE); also elsewhere on the board
/IO16: U3.1 (RO); also elsewhere on the board
/IO17: U3.4 (DI); also elsewhere on the board
/MCU_RXD0: R3.1; also elsewhere on the board
/MCU_TXD0: R2.1; also elsewhere on the board
/UART_DTR: Q1.4.2 (E), R4.1, U1.13 (~DTR)
/UART_RTS: Q1.3.2 (E), R5.1, U1.14 (~RTS)
/UART_RXD: R2.2, R3.2.1, R5.2.2
/UART_TXD: R3.2, R3.1.1, R5.1.2
GND: BOOT1.1, C2.1.2, C2.2.2, C3.3.1, C3.4.1, C13.2, D1.1 (K), D5.3.1 (K), D5.4.1 (K), J22.0 (PAD), J22.7, R14.2, RST1.1, U1.1 (GND), U2.1.1 (GND), U3.5 (GND); also elsewhere on the board
unnamed: D1.2 (A), R2.1.2
unnamed: D5.3.2 (A), R5.1.1
unnamed: D5.4.2 (A), R5.2.1
unnamed: Q1.3.1 (B), R4.2
unnamed: Q1.4.1 (B), R5.2
unnamed: R3.2.2, U1.3 (RXD)
unnamed: R3.1.2, U1.2 (TXD)

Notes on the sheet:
5V->3.3V
Boot
USB-UART
RESET
